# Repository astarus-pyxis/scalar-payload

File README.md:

# scalar-payload

SCALAR V is an experimental rocket made by students from the Supaéro Space Section in 2024. There were two payloads onboard this rocket, a Cansat with a particle matter sensor and a muon detector.

This repository provides the files and datasheets used to conceive the payloads of our experimental rocket SCALAR V.

Detailed information about this project can be found in the Final Report provided in this repository.

For complementary information, e-mail me at florian.topeza@student.isae-supaero.fr

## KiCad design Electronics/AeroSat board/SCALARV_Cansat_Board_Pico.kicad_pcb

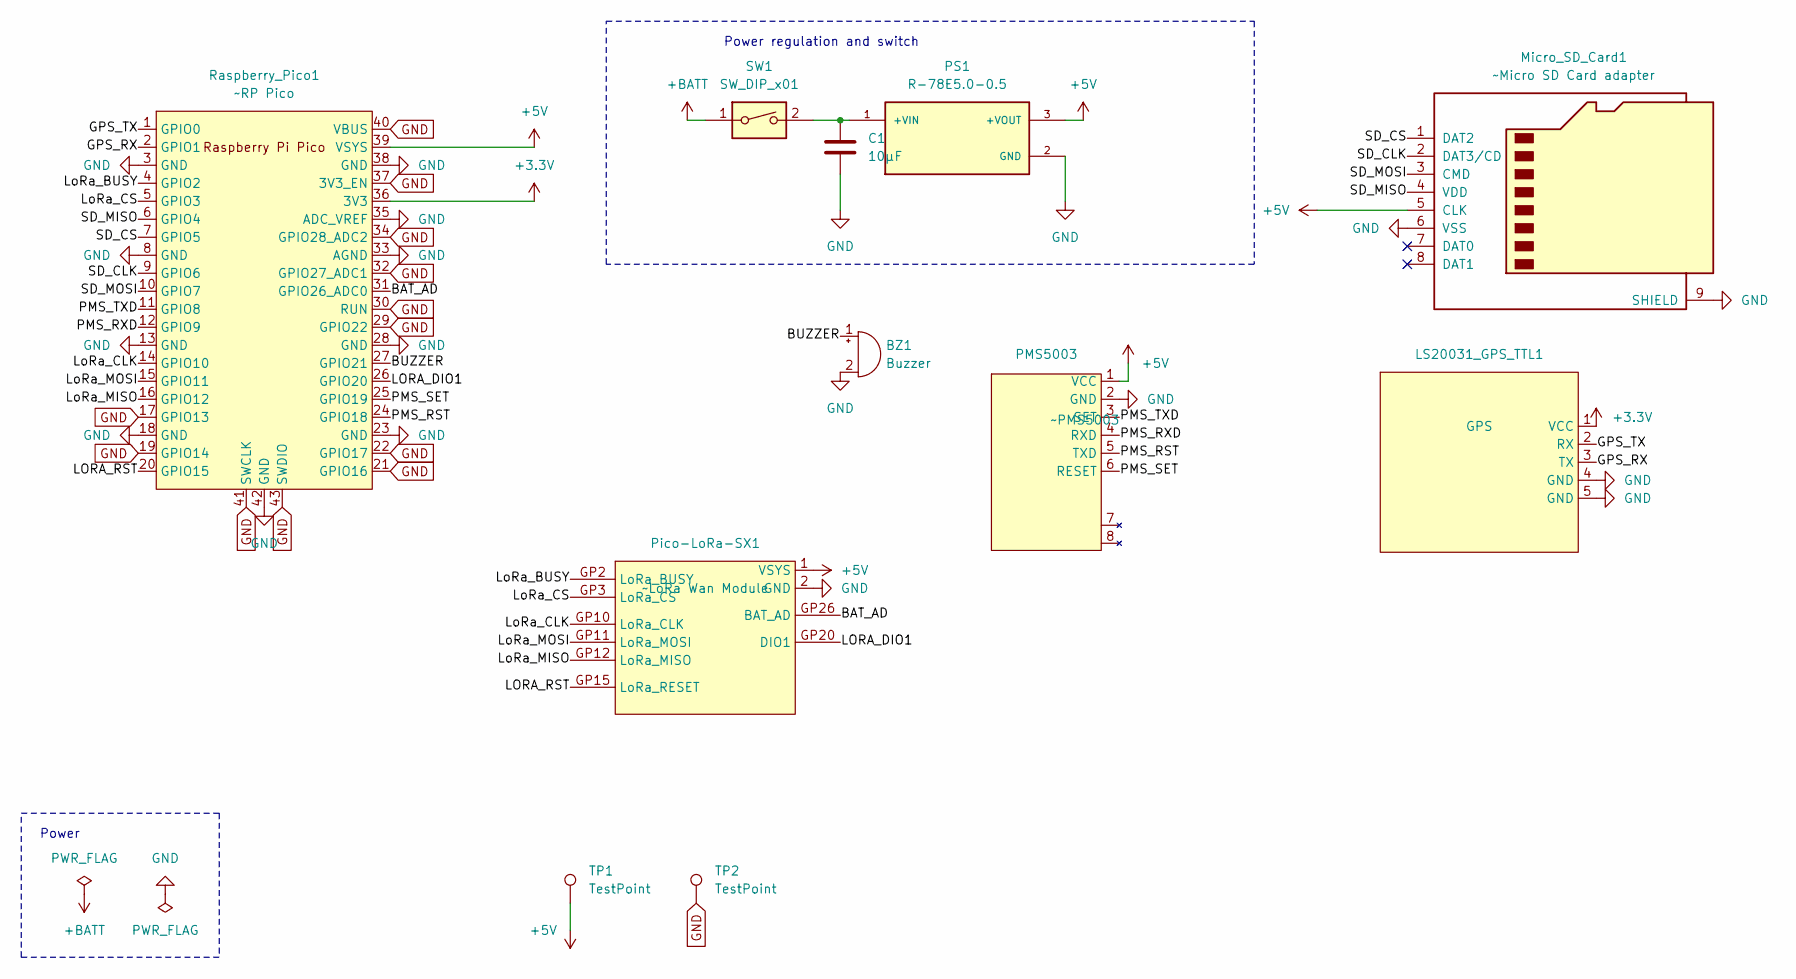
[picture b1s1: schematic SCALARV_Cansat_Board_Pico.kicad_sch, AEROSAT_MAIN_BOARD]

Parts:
BZ1: Buzzer; Buzzer_12x9.5RM7.6
C1: 10µF; FA23
LS20031_GPS_TTL1: GPS; LS20031_GPS_Vertical
Micro_SD_Card1: ~Micro SD Card adapter; Catalex_microSD_adaptater
PMS5003: ~PMS5003; PIM477
PS1: R-78E5.0-0.5; CONV_R-78E5.0-0.5; PARTREV 4
Pico-LoRa-SX1: ~LoRa Wan Module
Raspberry_Pico1: ~RP Pico; RPi_Pico_SMD_TH
SW1: SW_DIP_x01; SW_DIP_SPSTx01_Slide_9.78x4.72mm_W7.62mm_P2.54mm
TP1, TP2: TestPoint; TestPoint_Pad_D1.0mm

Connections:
+3.3V: LS20031_GPS_TTL1.1 (VCC), Raspberry_Pico1.36 (3V3)
+5V: Micro_SD_Card1.5 (CLK), PMS5003.1 (VCC), PS1.3 (+VOUT), Pico-LoRa-SX1.1 (VSYS), Raspberry_Pico1.39 (VSYS), TP1.1
+BATT: SW1.1
/BAT_AD: Pico-LoRa-SX1.GP26 (BAT_AD), Raspberry_Pico1.31 (GPIO26_ADC0)
/BUZZER: BZ1.1 (+), Raspberry_Pico1.27 (GPIO21)
/GPS_RX: LS20031_GPS_TTL1.3 (TX), Raspberry_Pico1.2 (GPIO1)
/GPS_TX: LS20031_GPS_TTL1.2 (RX), Raspberry_Pico1.1 (GPIO0)
/LORA_DIO1: Pico-LoRa-SX1.GP20 (DIO1), Raspberry_Pico1.26 (GPIO20)
/LORA_RST: Pico-LoRa-SX1.GP15 (LoRa_RESET), Raspberry_Pico1.20 (GPIO15)
/LoRa_BUSY: Pico-LoRa-SX1.GP2 (LoRa_BUSY), Raspberry_Pico1.4 (GPIO2)
/LoRa_CLK: Pico-LoRa-SX1.GP10 (LoRa_CLK), Raspberry_Pico1.14 (GPIO10)
/LoRa_CS: Pico-LoRa-SX1.GP3 (LoRa_CS), Raspberry_Pico1.5 (GPIO3)
/LoRa_MISO: Pico-LoRa-SX1.GP12 (LoRa_MISO), Raspberry_Pico1.16 (GPIO12)
/LoRa_MOSI: Pico-LoRa-SX1.GP11 (LoRa_MOSI), Raspberry_Pico1.15 (GPIO11)
/PMS_RST: PMS5003.5 (TXD), Raspberry_Pico1.24 (GPIO18)
/PMS_RXD: PMS5003.4 (RXD), Raspberry_Pico1.12 (GPIO9)
/PMS_SET: PMS5003.6 (RESET), Raspberry_Pico1.25 (GPIO19)
/PMS_TXD: PMS5003.3 (SET), Raspberry_Pico1.11 (GPIO8)
/SD_CLK: Micro_SD_Card1.2 (DAT3/CD), Raspberry_Pico1.9 (GPIO6)
/SD_CS: Micro_SD_Card1.1 (DAT2), Raspberry_Pico1.7 (GPIO5)
/SD_MISO: Micro_SD_Card1.4 (VDD), Raspberry_Pico1.6 (GPIO4)
/SD_MOSI: Micro_SD_Card1.3 (CMD), Raspberry_Pico1.10 (GPIO7)
GND: BZ1.2 (-), C1.2, LS20031_GPS_TTL1.4 (GND), LS20031_GPS_TTL1.5 (GND), Micro_SD_Card1.6 (VSS), Micro_SD_Card1.9 (SHIELD), PMS5003.2 (GND), PS1.2 (GND), Pico-LoRa-SX1.2 (GND), Raspberry_Pico1.3 (GND), Raspberry_Pico1.8 (GND), Raspberry_Pico1.13 (GND), Raspberry_Pico1.17 (GPIO13), Raspberry_Pico1.18 (GND), Raspberry_Pico1.19 (GPIO14), Raspberry_Pico1.21 (GPIO16), Raspberry_Pico1.22 (GPIO17), Raspberry_Pico1.23 (GND), Raspberry_Pico1.28 (GND), Raspberry_Pico1.29 (GPIO22), Raspberry_Pico1.30 (RUN), Raspberry_Pico1.32 (GPIO27_ADC1), Raspberry_Pico1.33 (AGND), Raspberry_Pico1.34 (GPIO28_ADC2), Raspberry_Pico1.35 (ADC_VREF), Raspberry_Pico1.37 (3V3_EN), Raspberry_Pico1.38 (GND), Raspberry_Pico1.40 (VBUS), Raspberry_Pico1.41 (SWCLK), Raspberry_Pico1.42 (GND), Raspberry_Pico1.43 (SWDIO), TP2.1
unnamed: C1.1, PS1.1 (+VIN), SW1.2

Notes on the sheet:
Power regulation and switch
Power

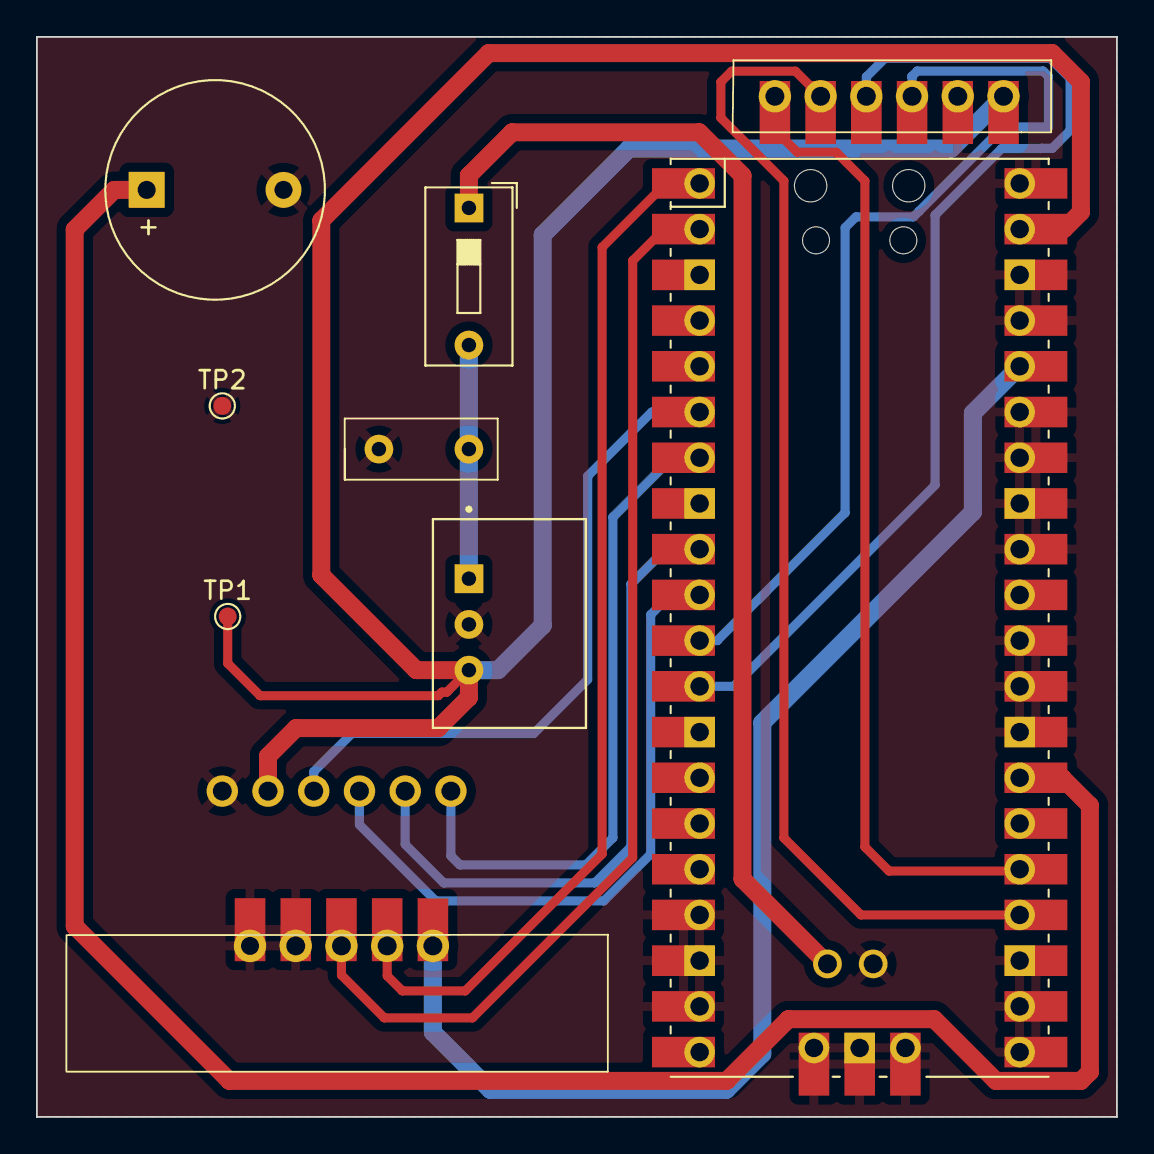
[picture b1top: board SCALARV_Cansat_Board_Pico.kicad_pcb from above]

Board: 2 copper layers, 60.0 x 60.0 mm, 10 parts (0 on the bottom side), 15 nets.

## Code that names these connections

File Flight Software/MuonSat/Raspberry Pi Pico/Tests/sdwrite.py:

import os
from machine import Pin, SPI
import sdcard

# Define SD card pins
SD_CS_PIN = 5
SD_SCK_PIN = 6
SD_MOSI_PIN = 7
SD_MISO_PIN = 4

# Initialize SPI
spi = SPI(0, baudrate=100000, sck=Pin(SD_SCK_PIN), mosi=Pin(SD_MOSI_PIN), miso=Pin(SD_MISO_PIN))

# Initialize SD card
sd = sdcard.SDCard(spi, Pin(SD_CS_PIN))
vfs = os.VfsFat(sd)
os.mount(vfs, '/sd')

# Example write to file
with open('/sd/test.txt', 'w') as f:
    f.write("Hello, world!\n")

# Example read from file
with open('/sd/test.txt', 'r') as f:
    print(f.read())

# Unmount SD card
os.umount('/sd')

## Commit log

2024-07-20 Updated reports
2024-10-21 MàJ pour SCAE
    Corrigé SCALAR V-a en SCALAR V
2024-10-21 Dossier reports
    Organisation du répertoire
2025-07-16 Reorganised repo
